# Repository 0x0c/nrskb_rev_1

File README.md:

# nrskb
no right shift keyboard

## Edit Layout
Use [Keyboard Layout Editor](http://www.keyboard-layout-editor.com/#/gists/df1fd062147ef462e2a68a1746d3611c)

## Build Firmware
Use [Keyboard Firmware Builder](https://kbfirmware.com) and load `nsrkbrev1.json`.

## Acknowledgement
- [yskoht/keyboard-layouter](https://github.com/yskoht/keyboard-layouter)

## Note

- [1行もコードを書かずに自作キーボードを作る](https://zenn.dev/0x0c/articles/4e4e428d79287d4556b2)

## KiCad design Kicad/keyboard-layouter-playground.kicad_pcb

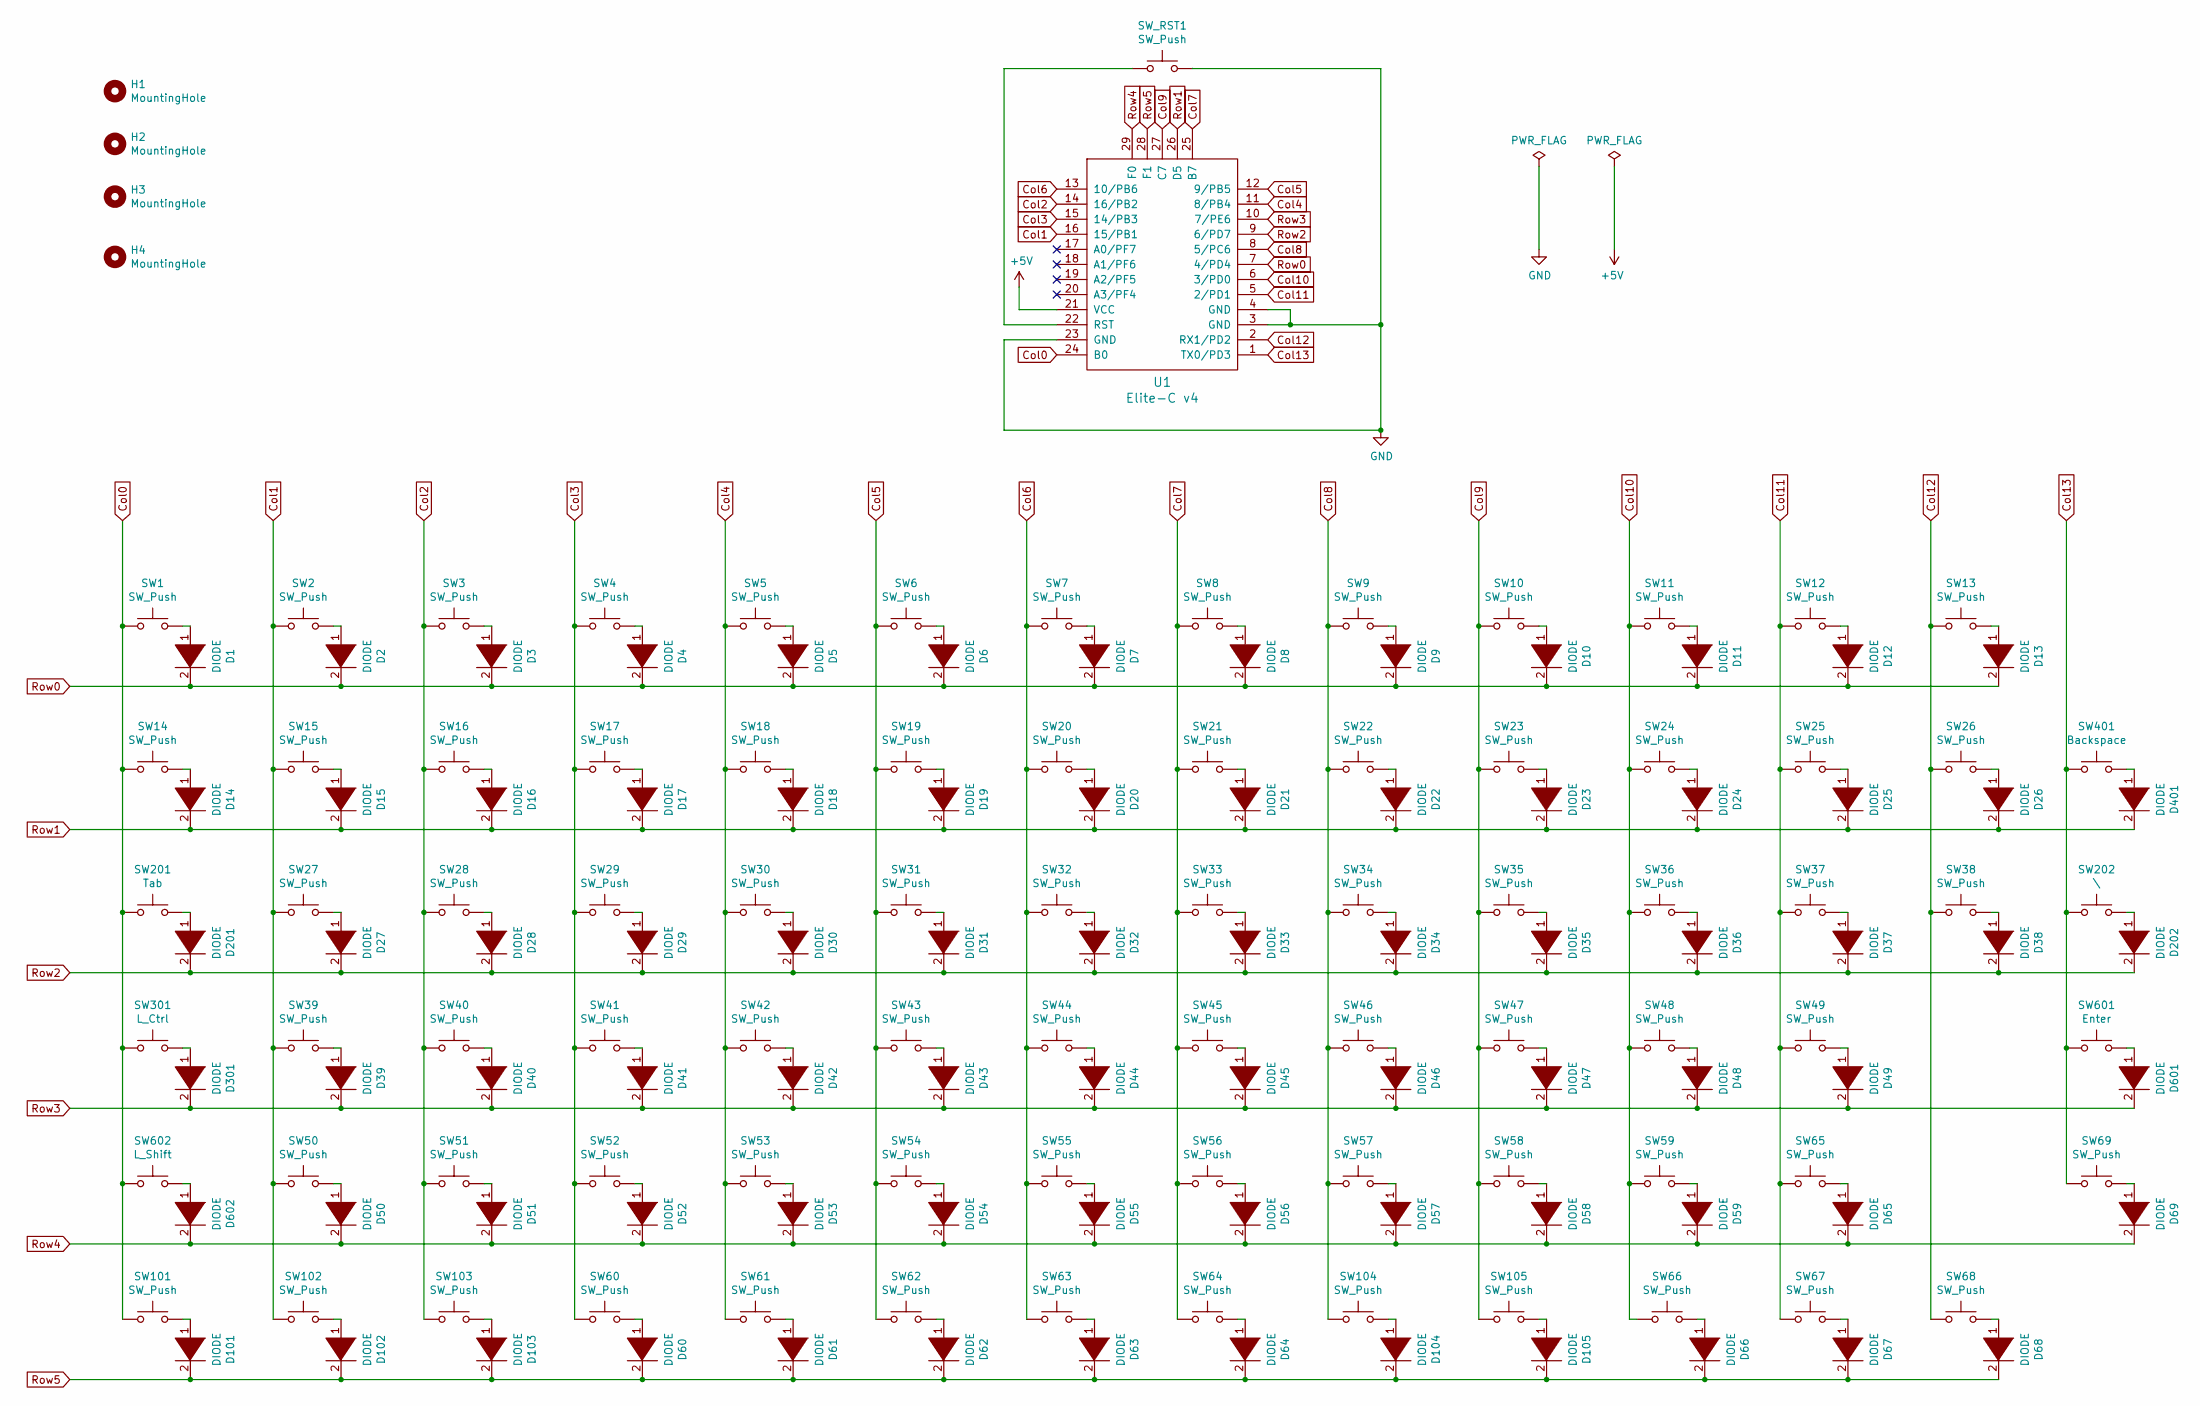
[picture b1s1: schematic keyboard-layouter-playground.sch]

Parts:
D1, D2, D3, D4, D5, D6, D7, D8, D9, D10, D11, D12, D13, D14, D15, D16, D17, D18, D19, D20, D21, D22, D23, D24, D25, D26, D27, D28, D29, D30, D31, D32, D33, D34, D35, D36, D37, D38, D39, D40, D41, D42, D43, D44, D45, D46, D47, D48, D49, D50, D51, D52, D53, D54, D55, D56, D57, D58, D59, D60, D61, D62, D63, D64, D65, D66, D67, D68, D69, D101, D102, D103, D104, D105, D201, D202, D301, D401, D601, D602: DIODE; D_1206_3216Metric_Pad1.42x1.75mm_HandSolder
H1, H2, H3, H4: MountingHole; MountingHole_3.2mm_M3
SW1, SW2, SW3, SW4, SW5, SW6, SW7, SW8, SW9, SW10, SW11, SW12, SW13, SW14, SW15, SW16, SW17, SW18, SW19, SW20, SW21, SW22, SW23, SW24, SW25, SW26, SW27, SW28, SW29, SW30, SW31, SW32, SW33, SW34, SW35, SW36, SW37, SW38, SW39, SW40, SW41, SW42, SW43, SW44, SW45, SW46, SW47, SW48, SW49, SW50, SW51, SW52, SW53, SW54, SW55, SW56, SW57, SW58, SW59, SW60, SW61, SW62, SW63, SW64, SW65, SW66, SW67, SW68, SW69: SW_Push; MXOnly-1U-Hotswap
SW101, SW102, SW103, SW104, SW105: SW_Push; MXOnly-1.25U-Hotswap
SW201: Tab; MXOnly-1.5U-Hotswap
SW202: \\; MXOnly-1.5U-Hotswap
SW301: L_Ctrl; MXOnly-1.75U-Hotswap
SW401: Backspace; MXOnly-2U-Hotswap
SW601: Enter; MXOnly-2.25U-Hotswap
SW602: L_Shift; MXOnly-2.25U-Hotswap
SW_RST1: SW_Push; SKRPACE010
U1: Elite-C v4; Elite-C

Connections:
Col0: SW1.1, SW14.1, SW101.1, SW201.1, SW301.1, SW602.1, U1.24 (B0)
Col1: SW2.1, SW15.1, SW27.1, SW39.1, SW50.1, SW102.1, U1.16 (15/PB1)
Col2: SW3.1, SW16.1, SW28.1, SW40.1, SW51.1, SW103.1, U1.14 (16/PB2)
Col3: SW4.1, SW17.1, SW29.1, SW41.1, SW52.1, SW60.1, U1.15 (14/PB3)
Col4: SW5.1, SW18.1, SW30.1, SW42.1, SW53.1, SW61.1, U1.11 (8/PB4)
Col5: SW6.1, SW19.1, SW31.1, SW43.1, SW54.1, SW62.1, U1.12 (9/PB5)
Col6: SW7.1, SW20.1, SW32.1, SW44.1, SW55.1, SW63.1, U1.13 (10/PB6)
Col7: SW8.1, SW21.1, SW33.1, SW45.1, SW56.1, SW64.1, U1.25 (B7)
Col8: SW9.1, SW22.1, SW34.1, SW46.1, SW57.1, SW104.1, U1.8 (5/PC6)
Col9: SW10.1, SW23.1, SW35.1, SW47.1, SW58.1, SW105.1, U1.27 (C7)
Col10: SW11.1, SW24.1, SW36.1, SW48.1, SW59.1, SW66.1, U1.6 (3/PD0)
Col11: SW12.1, SW25.1, SW37.1, SW49.1, SW65.1, SW67.1, U1.5 (2/PD1)
Col12: SW13.1, SW26.1, SW38.1, SW68.1, U1.2 (RX1/PD2)
Col13: SW69.1, SW202.1, SW401.1, SW601.1, U1.1 (TX0/PD3)
GND: SW_RST1.2, U1.3 (GND), U1.4 (GND), U1.23 (GND)
unnamed: D1.1 (K), SW1.2
unnamed: D2.1 (K), SW2.2
unnamed: D3.1 (K), SW3.2
unnamed: D4.1 (K), SW4.2
unnamed: D5.1 (K), SW5.2
unnamed: D6.1 (K), SW6.2
unnamed: D7.1 (K), SW7.2
unnamed: D8.1 (K), SW8.2
unnamed: D9.1 (K), SW9.2
unnamed: D10.1 (K), SW10.2
unnamed: D11.1 (K), SW11.2
unnamed: D12.1 (K), SW12.2
unnamed: D13.1 (K), SW13.2
unnamed: D14.1 (K), SW14.2
unnamed: D15.1 (K), SW15.2
unnamed: D16.1 (K), SW16.2
unnamed: D17.1 (K), SW17.2
unnamed: D18.1 (K), SW18.2
unnamed: D19.1 (K), SW19.2
unnamed: D20.1 (K), SW20.2
unnamed: D21.1 (K), SW21.2
unnamed: D22.1 (K), SW22.2
unnamed: D23.1 (K), SW23.2
unnamed: D24.1 (K), SW24.2
unnamed: D25.1 (K), SW25.2
unnamed: D26.1 (K), SW26.2
unnamed: D27.1 (K), SW27.2
unnamed: D28.1 (K), SW28.2
unnamed: D29.1 (K), SW29.2
unnamed: D30.1 (K), SW30.2
unnamed: D31.1 (K), SW31.2
unnamed: D32.1 (K), SW32.2
unnamed: D33.1 (K), SW33.2
unnamed: D34.1 (K), SW34.2
unnamed: D35.1 (K), SW35.2
unnamed: D36.1 (K), SW36.2
unnamed: D37.1 (K), SW37.2
unnamed: D38.1 (K), SW38.2
unnamed: D39.1 (K), SW39.2
unnamed: D40.1 (K), SW40.2
unnamed: D41.1 (K), SW41.2
unnamed: D42.1 (K), SW42.2
unnamed: D43.1 (K), SW43.2
unnamed: D44.1 (K), SW44.2
unnamed: D45.1 (K), SW45.2
unnamed: D46.1 (K), SW46.2
unnamed: D47.1 (K), SW47.2
unnamed: D48.1 (K), SW48.2
unnamed: D49.1 (K), SW49.2
unnamed: D50.1 (K), SW50.2
unnamed: D51.1 (K), SW51.2
unnamed: D52.1 (K), SW52.2
unnamed: D53.1 (K), SW53.2
unnamed: D54.1 (K), SW54.2
unnamed: D55.1 (K), SW55.2
unnamed: D56.1 (K), SW56.2
unnamed: D57.1 (K), SW57.2
unnamed: D58.1 (K), SW58.2
unnamed: D59.1 (K), SW59.2
unnamed: D60.1 (K), SW60.2
unnamed: D61.1 (K), SW61.2
unnamed: D62.1 (K), SW62.2
unnamed: D63.1 (K), SW63.2
unnamed: D64.1 (K), SW64.2
unnamed: D65.1 (K), SW65.2
unnamed: D66.1 (K), SW66.2
unnamed: D67.1 (K), SW67.2
unnamed: D68.1 (K), SW68.2
unnamed: D69.1 (K), SW69.2
unnamed: D101.1 (K), SW101.2
unnamed: D102.1 (K), SW102.2
unnamed: D103.1 (K), SW103.2
unnamed: D104.1 (K), SW104.2
unnamed: D105.1 (K), SW105.2
unnamed: D201.1 (K), SW201.2
unnamed: D202.1 (K), SW202.2
unnamed: D301.1 (K), SW301.2
unnamed: D401.1 (K), SW401.2
unnamed: D601.1 (K), SW601.2
unnamed: D602.1 (K), SW602.2
unnamed: SW_RST1.1, U1.22 (RST)
Row0: D1.2 (A), D2.2 (A), D3.2 (A), D4.2 (A), D5.2 (A), D6.2 (A), D7.2 (A), D8.2 (A), D9.2 (A), D10.2 (A), D11.2 (A), D12.2 (A), D13.2 (A), U1.7 (4/PD4)
Row1: D14.2 (A), D15.2 (A), D16.2 (A), D17.2 (A), D18.2 (A), D19.2 (A), D20.2 (A), D21.2 (A), D22.2 (A), D23.2 (A), D24.2 (A), D25.2 (A), D26.2 (A), D401.2 (A), U1.26 (D5)
Row2: D27.2 (A), D28.2 (A), D29.2 (A), D30.2 (A), D31.2 (A), D32.2 (A), D33.2 (A), D34.2 (A), D35.2 (A), D36.2 (A), D37.2 (A), D38.2 (A), D201.2 (A), D202.2 (A), U1.9 (6/PD7)
Row3: D39.2 (A), D40.2 (A), D41.2 (A), D42.2 (A), D43.2 (A), D44.2 (A), D45.2 (A), D46.2 (A), D47.2 (A), D48.2 (A), D49.2 (A), D301.2 (A), D601.2 (A), U1.10 (7/PE6)
Row4: D50.2 (A), D51.2 (A), D52.2 (A), D53.2 (A), D54.2 (A), D55.2 (A), D56.2 (A), D57.2 (A), D58.2 (A), D59.2 (A), D65.2 (A), D69.2 (A), D602.2 (A), U1.29 (F0)
Row5: D60.2 (A), D61.2 (A), D62.2 (A), D63.2 (A), D64.2 (A), D66.2 (A), D67.2 (A), D68.2 (A), D101.2 (A), D102.2 (A), D103.2 (A), D104.2 (A), D105.2 (A), U1.28 (F1)

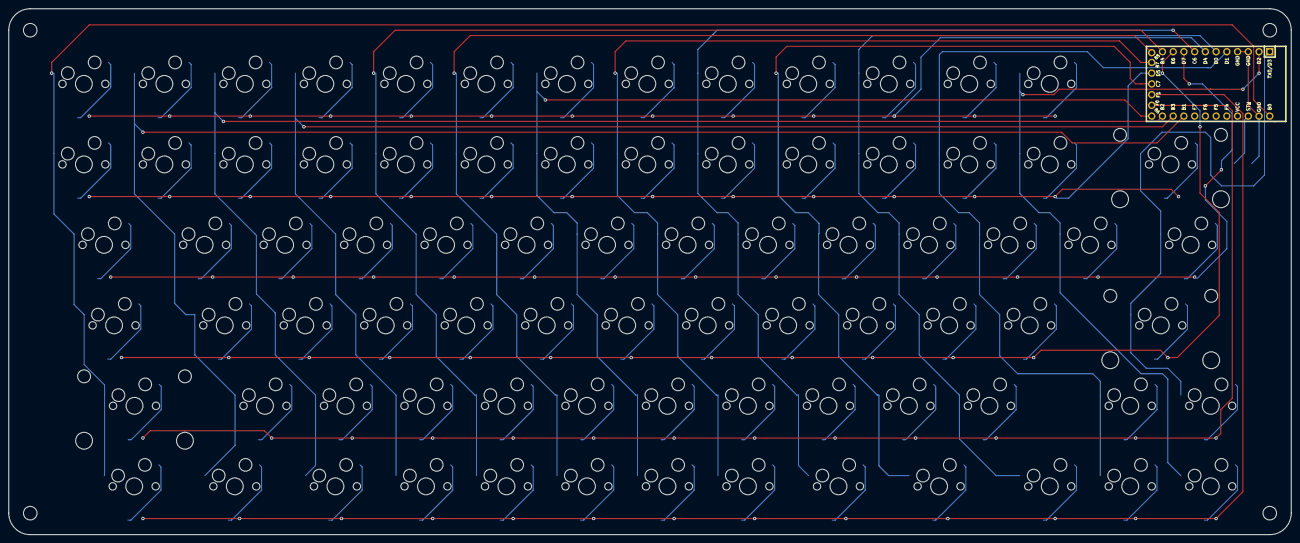
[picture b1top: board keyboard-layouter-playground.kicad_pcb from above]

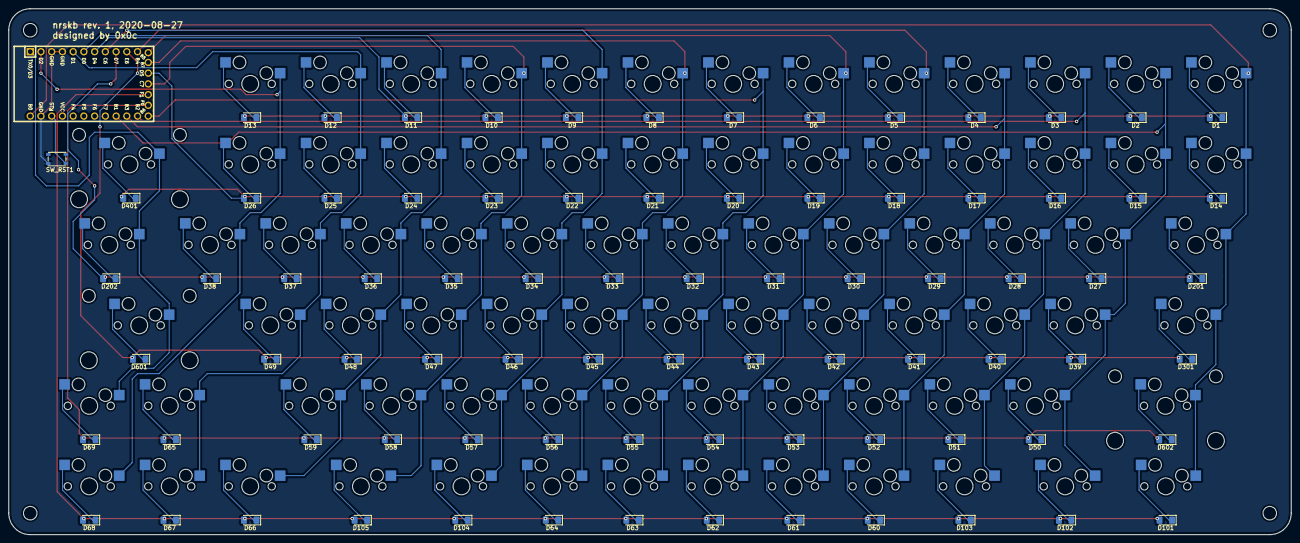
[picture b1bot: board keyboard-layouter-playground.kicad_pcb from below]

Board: 2 copper layers, 303.5 x 124.5 mm, 166 parts (81 on the bottom side), 102 nets.

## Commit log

2020-09-19 fix readme
2020-09-22 リポジトリを整理
2020-09-22 add frame
2020-09-22 add photo
